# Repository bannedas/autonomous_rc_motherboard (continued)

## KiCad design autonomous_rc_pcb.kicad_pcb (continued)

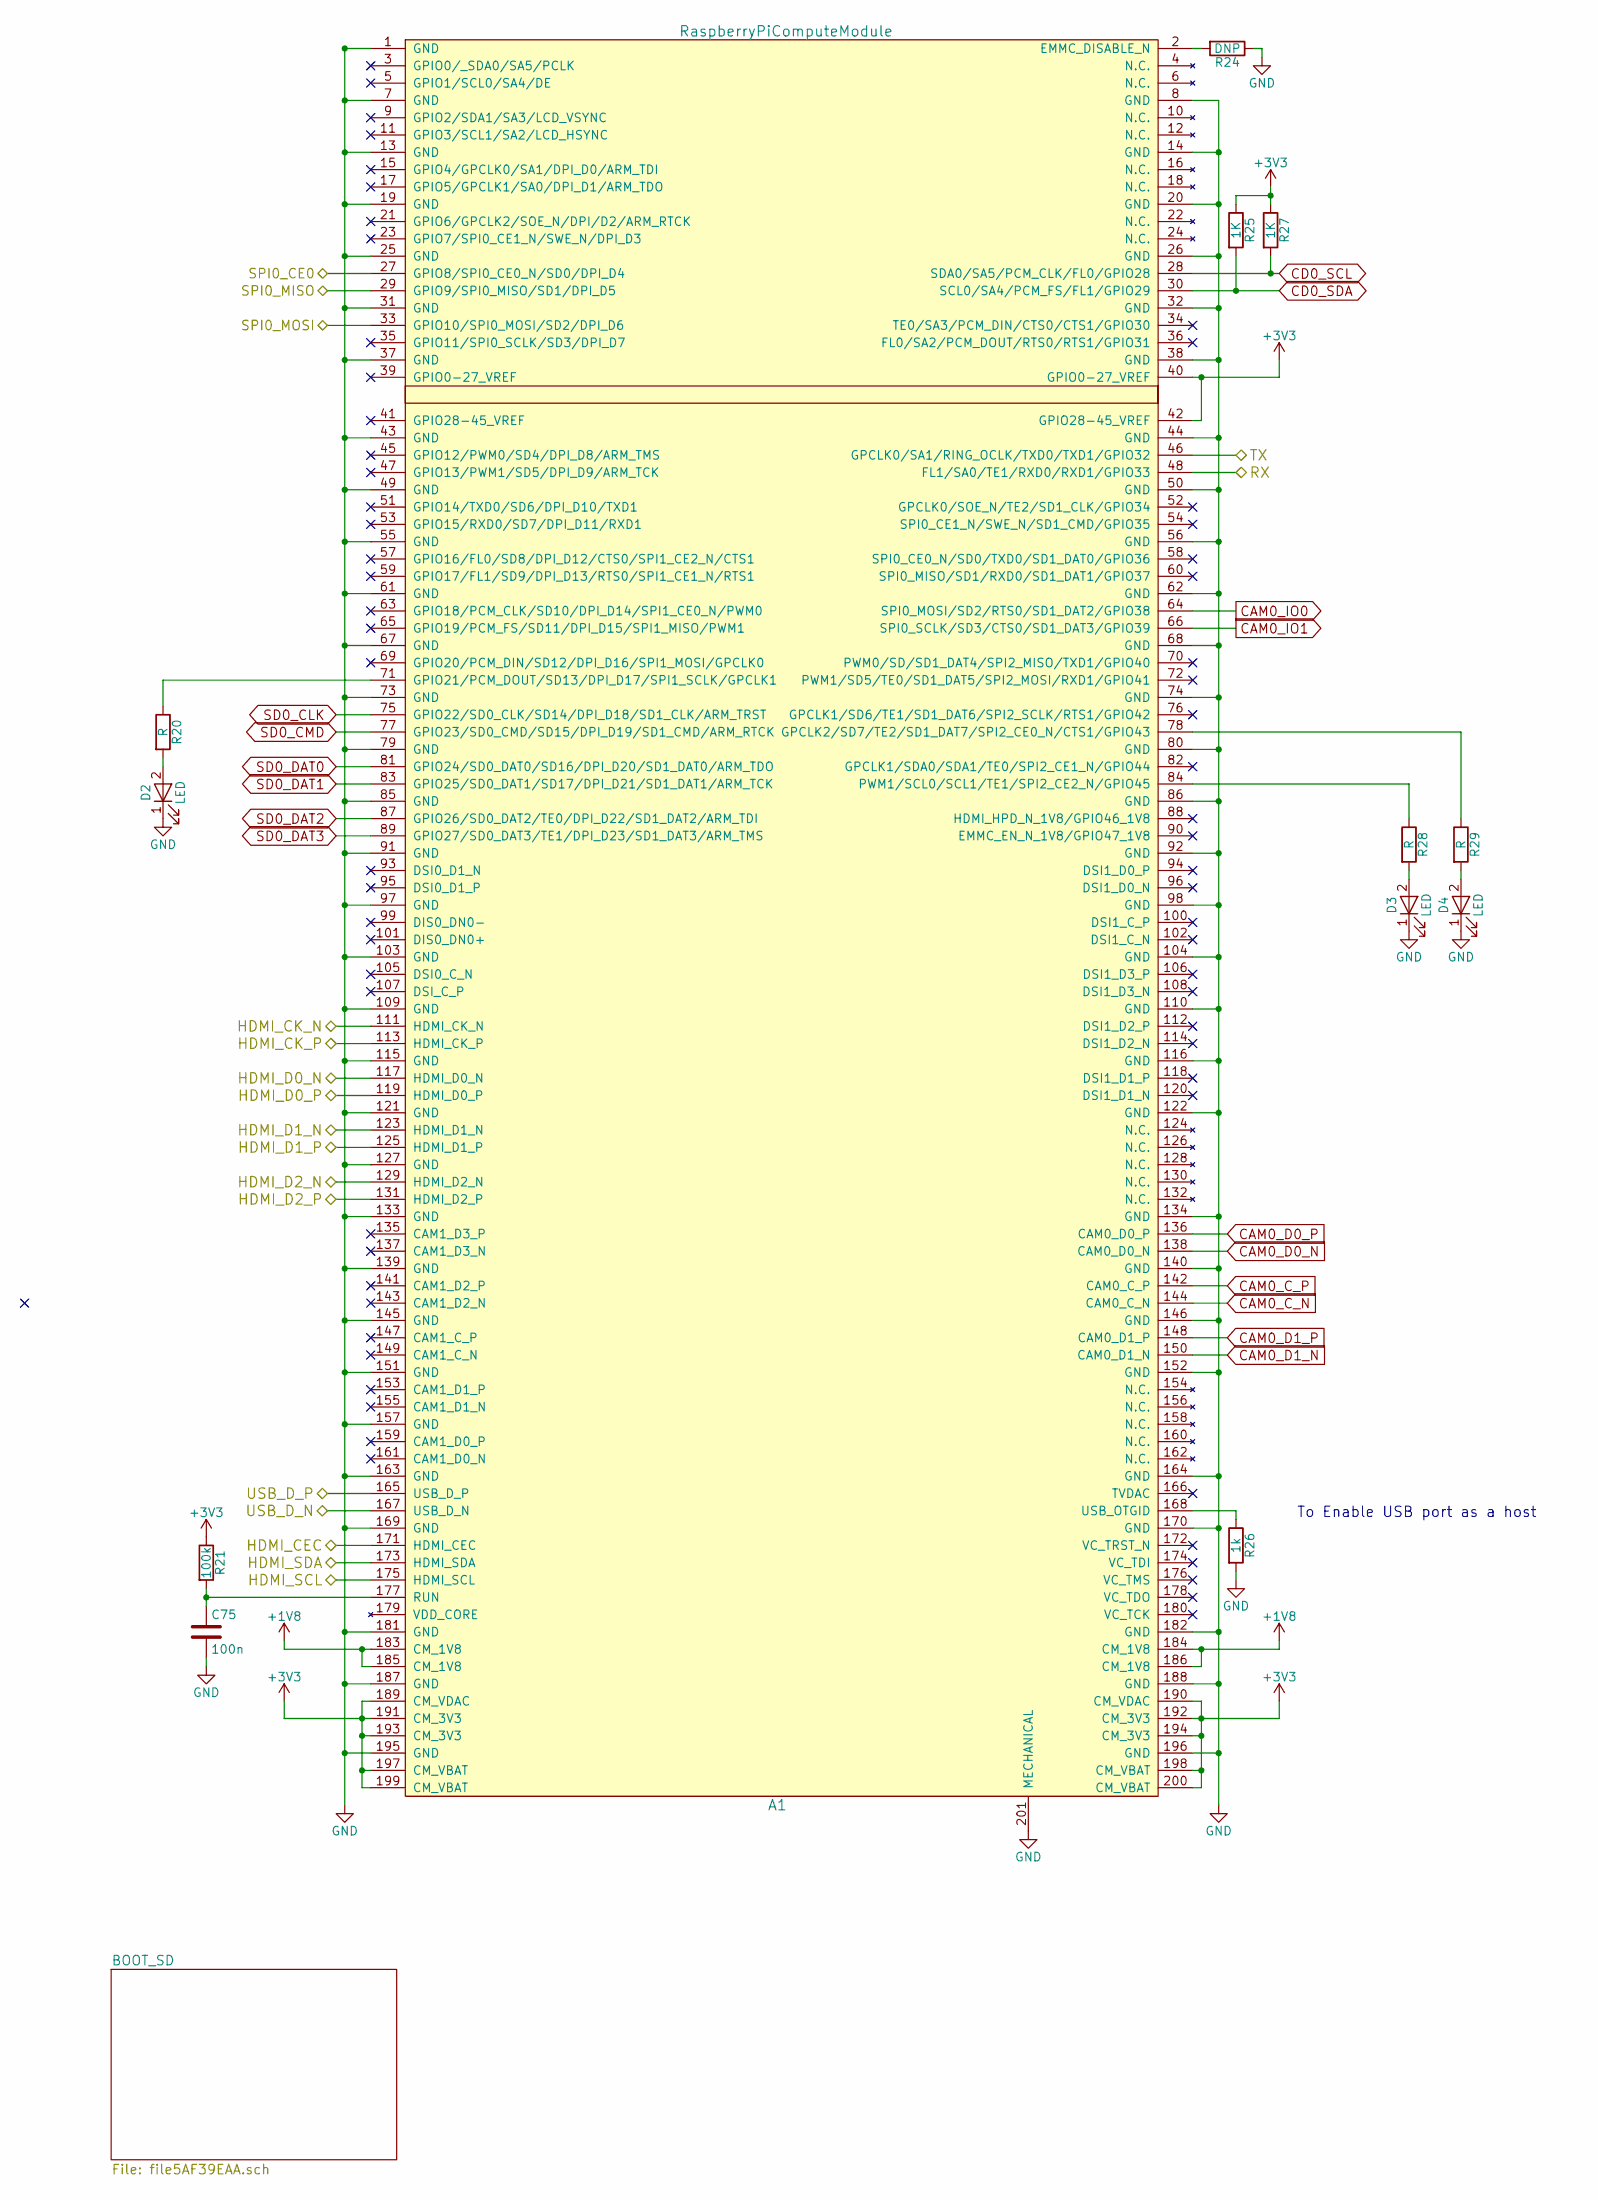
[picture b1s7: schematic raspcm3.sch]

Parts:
A1: RaspberryPiComputeModule; DDR2_TE_1473149-4
C75: 100n; C_0402
D2, D3, D4: LED; LED_0603
R20, R28, R29: R; R_0402
R21: 100k; R_0402
R24: DNP; R_0402
R25, R27: 1K; R_0402
R26: 1k; R_0402

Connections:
+1V8: A1.183 (CM_1V8), A1.184 (CM_1V8), A1.185 (CM_1V8), A1.186 (CM_1V8); also elsewhere on the board
/STM_RESET: A1.33 (GPIO10/SPI0_MOSI/SD2/DPI_D6); also elsewhere on the board
/STM_SWCLK: A1.27 (GPIO8/SPI0_CE0_N/SD0/DPI_D4); also elsewhere on the board
/STM_SWDIO: A1.29 (GPIO9/SPI0_MISO/SD1/DPI_D5); also elsewhere on the board
/UART_RX_GPS_RASP: A1.48 (FL1/SA0/TE1/RXD0/RXD1/GPIO33); also elsewhere on the board
/UART_TX_GPS_RASP: A1.46 (GPCLK0/SA1/RING_OCLK/TXD0/TXD1/GPIO32); also elsewhere on the board
/USB_HUB+: A1.165 (USB_D_P); also elsewhere on the board
/USB_HUB-: A1.167 (USB_D_N); also elsewhere on the board
/raspcm3/HDMI_CEC: A1.171 (HDMI_CEC); also elsewhere on the board
/raspcm3/HDMI_CK_N: A1.111 (HDMI_CK_N); also elsewhere on the board
/raspcm3/HDMI_CK_P: A1.113 (HDMI_CK_P); also elsewhere on the board
/raspcm3/HDMI_D0_N: A1.117 (HDMI_D0_N); also elsewhere on the board
/raspcm3/HDMI_D0_P: A1.119 (HDMI_D0_P); also elsewhere on the board
/raspcm3/HDMI_D1_N: A1.123 (HDMI_D1_N); also elsewhere on the board
/raspcm3/HDMI_D1_P: A1.125 (HDMI_D1_P); also elsewhere on the board
/raspcm3/HDMI_D2_N: A1.129 (HDMI_D2_N); also elsewhere on the board
/raspcm3/HDMI_D2_P: A1.131 (HDMI_D2_P); also elsewhere on the board
/raspcm3/HDMI_SCL: A1.175 (HDMI_SCL); also elsewhere on the board
/raspcm3/HDMI_SDA: A1.173 (HDMI_SDA); also elsewhere on the board
CAM0_C_N: A1.144 (CAM0_C_N); also elsewhere on the board
CAM0_C_P: A1.142 (CAM0_C_P); also elsewhere on the board
CAM0_D0_N: A1.138 (CAM0_D0_N); also elsewhere on the board
CAM0_D0_P: A1.136 (CAM0_D0_P); also elsewhere on the board
CAM0_D1_N: A1.150 (CAM0_D1_N); also elsewhere on the board
CAM0_D1_P: A1.148 (CAM0_D1_P); also elsewhere on the board
CAM0_IO0: A1.64 (SPI0_MOSI/SD2/RTS0/SD1_DAT2/GPIO38); also elsewhere on the board
CAM0_IO1: A1.66 (SPI0_SCLK/SD3/CTS0/SD1_DAT3/GPIO39); also elsewhere on the board
CD0_SCL: A1.28 (SDA0/SA5/PCM_CLK/FL0/GPIO28), R27.2; also elsewhere on the board
CD0_SDA: A1.30 (SCL0/SA4/PCM_FS/FL1/GPIO29), R25.2; also elsewhere on the board
GND: A1.1 (GND), A1.7 (GND), A1.8 (GND), A1.13 (GND), A1.14 (GND), A1.19 (GND), A1.20 (GND), A1.25 (GND), A1.26 (GND), A1.31 (GND), A1.32 (GND), A1.37 (GND), A1.38 (GND), A1.43 (GND), A1.44 (GND), A1.49 (GND), A1.50 (GND), A1.55 (GND), A1.56 (GND), A1.61 (GND), A1.62 (GND), A1.67 (GND), A1.68 (GND), A1.73 (GND), A1.74 (GND), A1.79 (GND), A1.80 (GND), A1.85 (GND), A1.86 (GND), A1.91 (GND), A1.92 (GND), A1.97 (GND), A1.98 (GND), A1.103 (GND), A1.104 (GND), A1.109 (GND), A1.110 (GND), A1.115 (GND), A1.116 (GND), A1.121 (GND), A1.122 (GND), A1.127 (GND), A1.133 (GND), A1.134 (GND), A1.139 (GND), A1.140 (GND), A1.145 (GND), A1.146 (GND), A1.151 (GND), A1.152 (GND), A1.157 (GND), A1.163 (GND), A1.164 (GND), A1.169 (GND), A1.170 (GND), A1.181 (GND), A1.182 (GND), A1.187 (GND), A1.188 (GND), A1.195 (GND), A1.196 (GND), A1.201 (MECHANICAL), C75.2, D2.1 (K), D3.1 (K), D4.1 (K), R24.1, R26.2; also elsewhere on the board
unnamed: A1.2 (EMMC_DISABLE_N), R24.2
unnamed: A1.71 (GPIO21/PCM_DOUT/SD13/DPI_D17/SPI1_SCLK/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), R20.1
unnamed: A1.78 (GPCLK2/SD7/TE2/SD1_DAT7/SPI2_CE0_N/CTS1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), R29.1
unnamed: A1.84 (PWM1/SCL0/SCL1/TE1/SPI2_CE2_N/GPIO45), R28.1
unnamed: A1.168 (USB_OTGID), R26.1
unnamed: A1.177 (RUN), C75.1, R21.2
unnamed: D2.2 (A), R20.2
unnamed: D3.2 (A), R28.2
unnamed: D4.2 (A), R29.2
SD0_CLK: A1.75 (GPIO22/SD0_CLK/SD14/DPI_D18/SD1_CLK/ARM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); also elsewhere on the board
SD0_CMD: A1.77 (GPIO23/SD0_CMD/SD15/DPI_D19/SD1_CMD/ARM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); also elsewhere on the board
SD0_DAT0: A1.81 (GPIO24/SD0_DAT0/SD16/DPI_D20/SD1_DAT0/A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); also elsewhere on the board
SD0_DAT1: A1.83 (GPIO25/SD0_DAT1/SD17/DPI_D21/SD1_DAT1/A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); also elsewhere on the board
SD0_DAT2: A1.87 (GPIO26/SD0_DAT2/TE0/DPI_D22/SD1_DAT2/AR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); also elsewhere on the board
SD0_DAT3: A1.89 (GPIO27/SD0_DAT3/TE1/DPI_D23/SD1_DAT3/AR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); also elsewhere on the board

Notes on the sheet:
To Enable USB port as a host

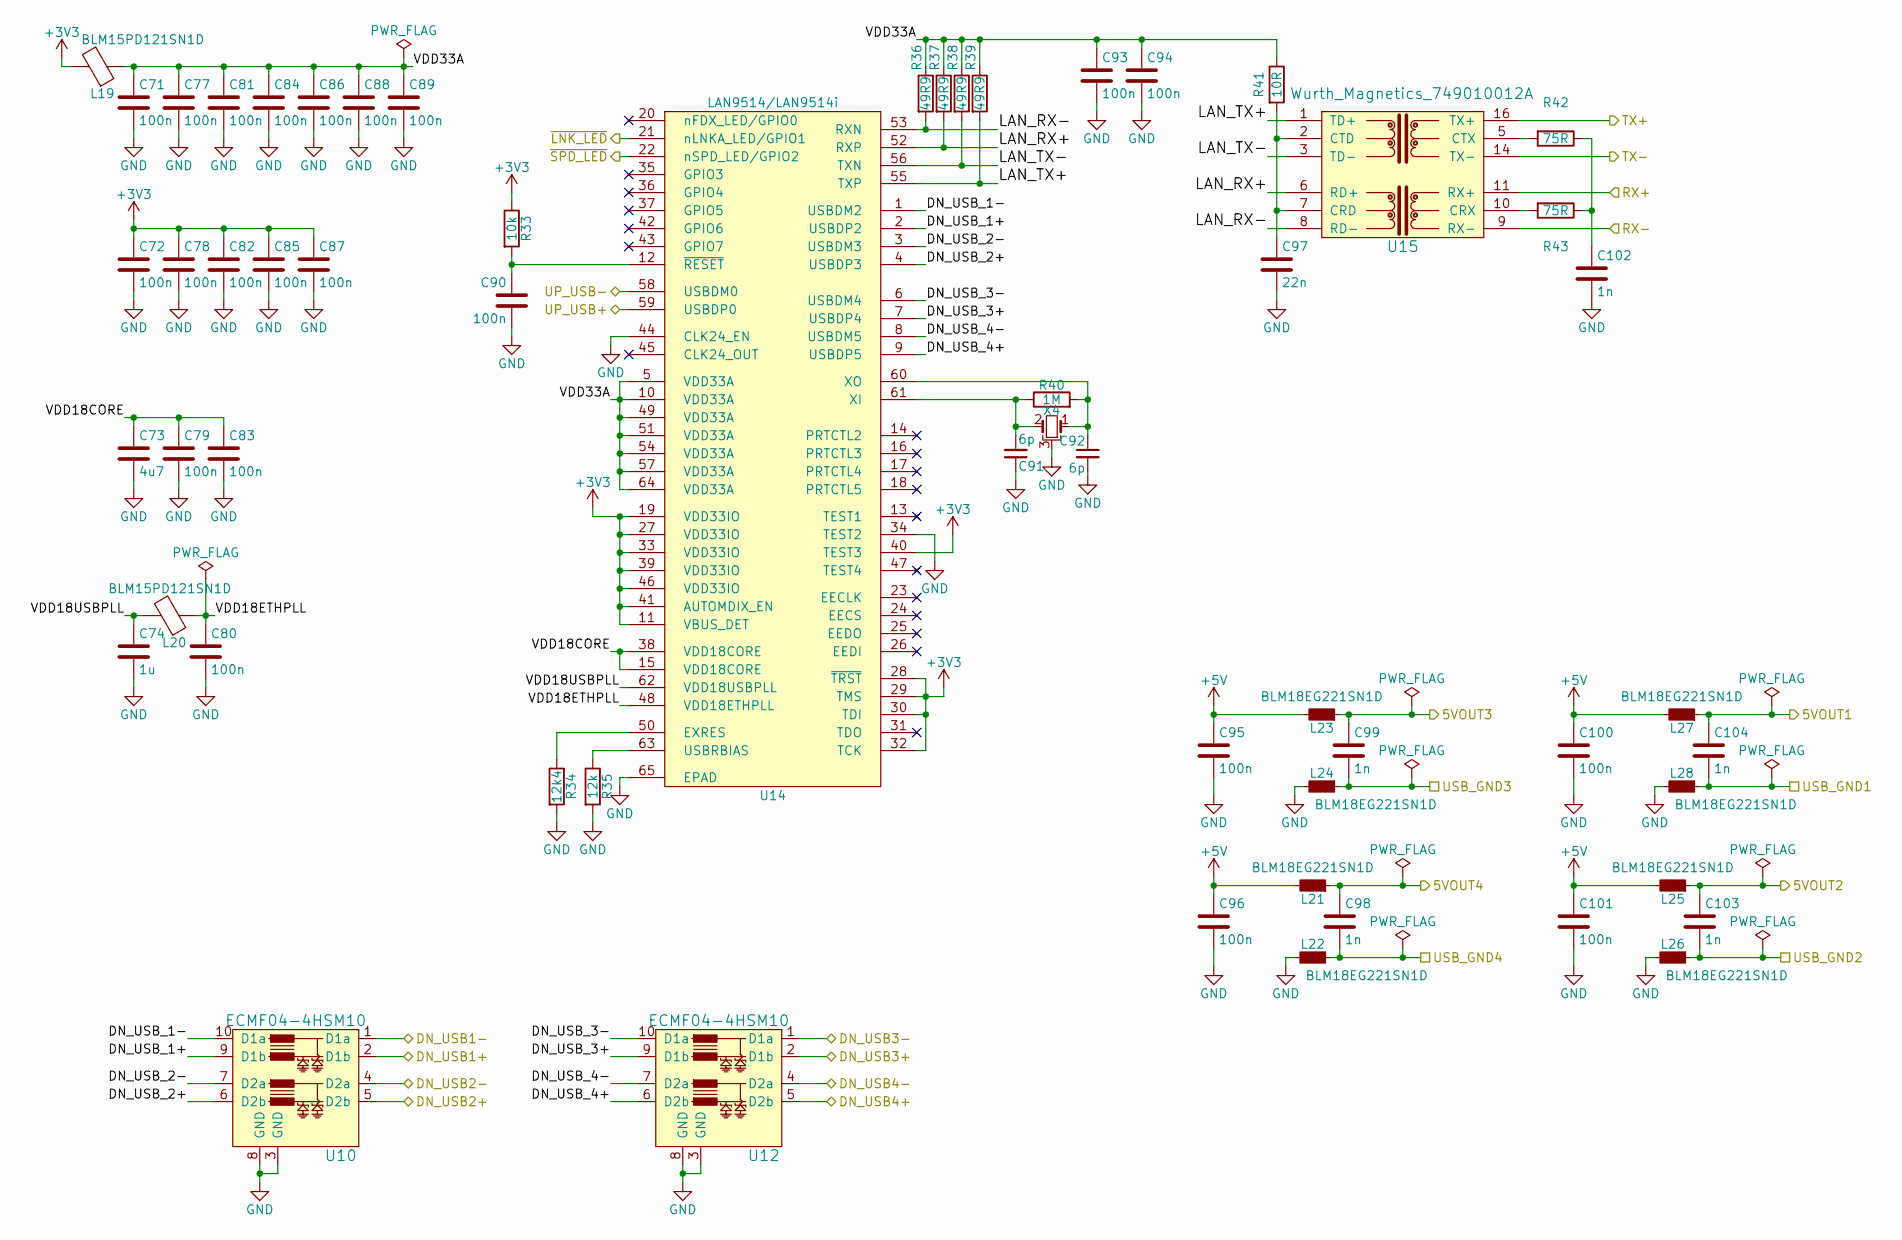
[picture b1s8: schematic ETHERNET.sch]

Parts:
C71, C72, C77, C78, C79, C80, C81, C82, C83, C84, C85, C86, C87, C88, C89, C90, C93, C94, C95, C96, C100, C101: 100n; C_0402
C73: 4u7; C_0603
C74: 1u; C_0402
C91, C92: 6p; C_0402
C97: 22n; C_0805
C98, C99, C103, C104: 1n; C_0402
C102: 1n; C_0805
L19, L20: BLM15PD121SN1D; R_0402
L21, L22, L23, L24, L25, L26, L27, L28: BLM18EG221SN1D; R_0603; MPN BLM18EG221SN1D
R33: 10k; R_0402
R34: 12k4; R_0402
R35: 12k; R_0402
R36, R37, R38, R39: 49R9; R_0402
R40: 1M; R_0402
R41: 10R; R_0402
R42, R43: 75R; R_0402
U10, U12: ECMF04-4HSM10; UDFN-10_1.35x2.6mm_Pitch0.5mm; MPN ECMF04-4HSM10
U14: LAN9514/LAN9514i; QFN-64-1EP_9x9mm_Pitch0.5mm; MPN LAN9514-JZX
U15: Wurth_Magnetics_749010012A; Wurth_749010012A; MPN 749010012A
X4: XRCGB25M000F2P00R0; XRCGB

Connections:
+5V: C95.1, C96.1, C100.1, C101.1, L21.2, L23.2, L25.2, L27.2; also elsewhere on the board
/ETHERNET/5VOUT1: C104.1, L27.1; also elsewhere on the board
/ETHERNET/5VOUT2: C103.1, L25.1; also elsewhere on the board
/ETHERNET/5VOUT3: C99.1, L23.1; also elsewhere on the board
/ETHERNET/5VOUT4: C98.1, L21.1; also elsewhere on the board
/ETHERNET/DN_USB1+: U10.2 (D1b); also elsewhere on the board
/ETHERNET/DN_USB1-: U10.1 (D1a); also elsewhere on the board
/ETHERNET/DN_USB2+: U10.5 (D2b); also elsewhere on the board
/ETHERNET/DN_USB2-: U10.4 (D2a); also elsewhere on the board
/ETHERNET/DN_USB3+: U12.2 (D1b); also elsewhere on the board
/ETHERNET/DN_USB3-: U12.1 (D1a); also elsewhere on the board
/ETHERNET/DN_USB4+: U12.5 (D2b); also elsewhere on the board
/ETHERNET/DN_USB4-: U12.4 (D2a); also elsewhere on the board
/ETHERNET/DN_USB_1+: U10.9 (D1b), U14.2 (USBDP2)
/ETHERNET/DN_USB_1-: U10.10 (D1a), U14.1 (USBDM2)
/ETHERNET/DN_USB_2+: U10.6 (D2b), U14.4 (USBDP3)
/ETHERNET/DN_USB_2-: U10.7 (D2a), U14.3 (USBDM3)
/ETHERNET/DN_USB_3+: U12.9 (D1b), U14.7 (USBDP4)
/ETHERNET/DN_USB_3-: U12.10 (D1a), U14.6 (USBDM4)
/ETHERNET/DN_USB_4+: U12.6 (D2b), U14.9 (USBDP5)
/ETHERNET/DN_USB_4-: U12.7 (D2a), U14.8 (USBDM5)
/ETHERNET/LAN_RX+: R37.2, U14.52 (RXP), U15.6 (RD+)
/ETHERNET/LAN_RX-: R36.2, U14.53 (RXN), U15.8 (RD-)
/ETHERNET/LAN_TX+: R39.2, U14.55 (TXP), U15.1 (TD+)
/ETHERNET/LAN_TX-: R38.2, U14.56 (TXN), U15.3 (TD-)
/ETHERNET/RX+: U15.11 (RX+); also elsewhere on the board
/ETHERNET/RX-: U15.9 (RX-); also elsewhere on the board
/ETHERNET/TX+: U15.16 (TX+); also elsewhere on the board
/ETHERNET/TX-: U15.14 (TX-); also elsewhere on the board
/ETHERNET/USB_GND1: C104.2, L28.1; also elsewhere on the board
/ETHERNET/USB_GND2: C103.2, L26.1; also elsewhere on the board
/ETHERNET/USB_GND3: C99.2, L24.1; also elsewhere on the board
/ETHERNET/USB_GND4: C98.2, L22.1; also elsewhere on the board
/ETHERNET/VDD18CORE: C73.1, C79.1, C83.1, U14.15 (VDD18CORE), U14.38 (VDD18CORE)
/ETHERNET/VDD18ETHPLL: C80.1, L20.1, U14.48 (VDD18ETHPLL)
/ETHERNET/VDD18USBPLL: C74.1, L20.2, U14.62 (VDD18USBPLL)
/ETHERNET/VDD33A: C71.1, C77.1, C81.1, C84.1, C86.1, C88.1, C89.1, C93.1, C94.1, L19.1, R36.1, R37.1, R38.1, R39.1, R41.1, U14.5 (VDD33A), U14.10 (VDD33A), U14.49 (VDD33A), U14.51 (VDD33A), U14.54 (VDD33A), U14.57 (VDD33A), U14.64 (VDD33A)
/ETHERNET/~LNK_LED: U14.21 (nLNKA_LED/GPIO1); also elsewhere on the board
/ETHERNET/~SPD_LED: U14.22 (nSPD_LED/GPIO2); also elsewhere on the board
/USB_ETHER+: U14.59 (USBDP0); also elsewhere on the board
/USB_ETHER-: U14.58 (USBDM0); also elsewhere on the board
GND: C71.2, C72.2, C73.2, C74.2, C77.2, C78.2, C79.2, C80.2, C81.2, C82.2, C83.2, C84.2, C85.2, C86.2, C87.2, C88.2, C89.2, C90.2, C91.1, C92.2, C93.2, C94.2, C95.2, C96.2, C97.2, C100.2, C101.2, C102.2, L22.2, L24.2, L26.2, L28.2, R34.2, R35.2, U10.3 (GND), U10.8 (GND), U12.3 (GND), U12.8 (GND), U14.34 (TEST2), U14.44 (CLK24_EN), U14.65 (EPAD), X4.3; also elsewhere on the board
unnamed: C90.1, R33.2, U14.12 (~RESET)
unnamed: C91.2, R40.1, U14.61 (XI), X4.2
unnamed: C92.1, R40.2, U14.60 (XO), X4.1
unnamed: C97.1, R41.2, U15.2 (CTD), U15.7 (CRD)
unnamed: C102.1, R42.1, R43.1
unnamed: R34.1, U14.50 (EXRES)
unnamed: R35.1, U14.63 (USBRBIAS)
unnamed: R42.2, U15.5 (CTX)
unnamed: R43.2, U15.10 (CRX)

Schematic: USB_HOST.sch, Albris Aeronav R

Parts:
C59, C60, C61, C62, C63, C65, C66, C69, C70: 100n; C_0402
C64: 9p; C_0603_1608Metric; MPN GRM1555C1H9R0CA01D
C67: 9p; C_0603_1608Metric
C68: 4u7 10V; C_0603
R14, R16, R17, R18, R19: 100k; R_0402
R15: 12k0; R_0402
U13: USB2514Bi; QFN36_5m5X5m5; MPN USB2514B/M2
X3: XRCGB24M000F2P00R0; XRCGB

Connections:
/STM_USB_N: U13.1 (USBDM_DN1/PRT_DIS_M1); also elsewhere on the board
/STM_USB_P: U13.2 (USBDP_DN1/PRT_DIS_P1); also elsewhere on the board
/UBLOX_USB+: U13.4 (USBDP_DN2/PRT_DIS_P2); also elsewhere on the board
/UBLOX_USB-: U13.3 (USBDM_DN2/PRT_DIS_M2); also elsewhere on the board
/USB_ETHER+: U13.7 (USBDP_DN3/PRT_DIS_P3); also elsewhere on the board
/USB_ETHER-: U13.6 (USBDM_DN3/PRT_DIS_M3); also elsewhere on the board
/USB_HUB+: U13.31 (USBUP_DP); also elsewhere on the board
/USB_HUB-: U13.30 (USBUP_DM); also elsewhere on the board
GND: C59.2, C60.2, C61.2, C62.2, C63.2, C64.1, C65.2, C66.2, C67.1, C68.2, C69.2, C70.2, R15.1, R16.2, R17.2, R18.2, R19.2, U13.37 (VSS(PAD)), X3.3; also elsewhere on the board
unnamed: C64.2, U13.33 (XTALIN/CLKIN), X3.1
unnamed: C66.1, R14.1, U13.26 (RESET_N)
unnamed: C67.2, U13.32 (XTALOUT), X3.2
unnamed: C69.1, U13.34 (PLLFILT)
unnamed: C70.1, U13.14 (CRFILT)
unnamed: R15.2, U13.35 (RBIAS)
unnamed: R16.1, U13.22 (SDA/SMBDATA/NON_REM1)
unnamed: R17.1, U13.28 (SUSP_IND/LOCAL_PWR/NON_REM0)
unnamed: R18.1, U13.25 (HS_IND/CFG_SEL1)
unnamed: R19.1, U13.24 (SCL/SMBCLK/CFG_SEL0)

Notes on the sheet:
pin 15

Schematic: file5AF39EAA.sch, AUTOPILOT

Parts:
C76: 100n; C_0402
J9: Micro_SD_Card; microSD_Card_Receptacle_Wurth_693072010801
U11: CM1624; UDFN-16-1EP_3.3x1.35mm_Pitch0.4mm

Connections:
GND: C76.2, J9.6 (VSS), J9.9 (SHIELD), U11.17 (GND); also elsewhere on the board
unnamed: C76.1, J9.4 (VDD), U11.4 (SDESD1)
unnamed: J9.1 (DAT2), U11.8 (SDData2)
unnamed: J9.2 (DAT3/CD), U11.7 (SDData3)
unnamed: J9.3 (CMD), U11.6 (SDCMD)
unnamed: J9.5 (CLK), U11.3 (SDCLK)
unnamed: J9.7 (DAT0), U11.2 (SDData0)
unnamed: J9.8 (DAT1), U11.1 (SDData1)
SD0_CLK: U11.14 (CLK); also elsewhere on the board
SD0_CMD: U11.11 (CMD); also elsewhere on the board
SD0_DAT0: U11.15 (DATA0); also elsewhere on the board
SD0_DAT1: U11.16 (DATA1); also elsewhere on the board
SD0_DAT2: U11.9 (Data2); also elsewhere on the board
SD0_DAT3: U11.10 (Data3); also elsewhere on the board

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
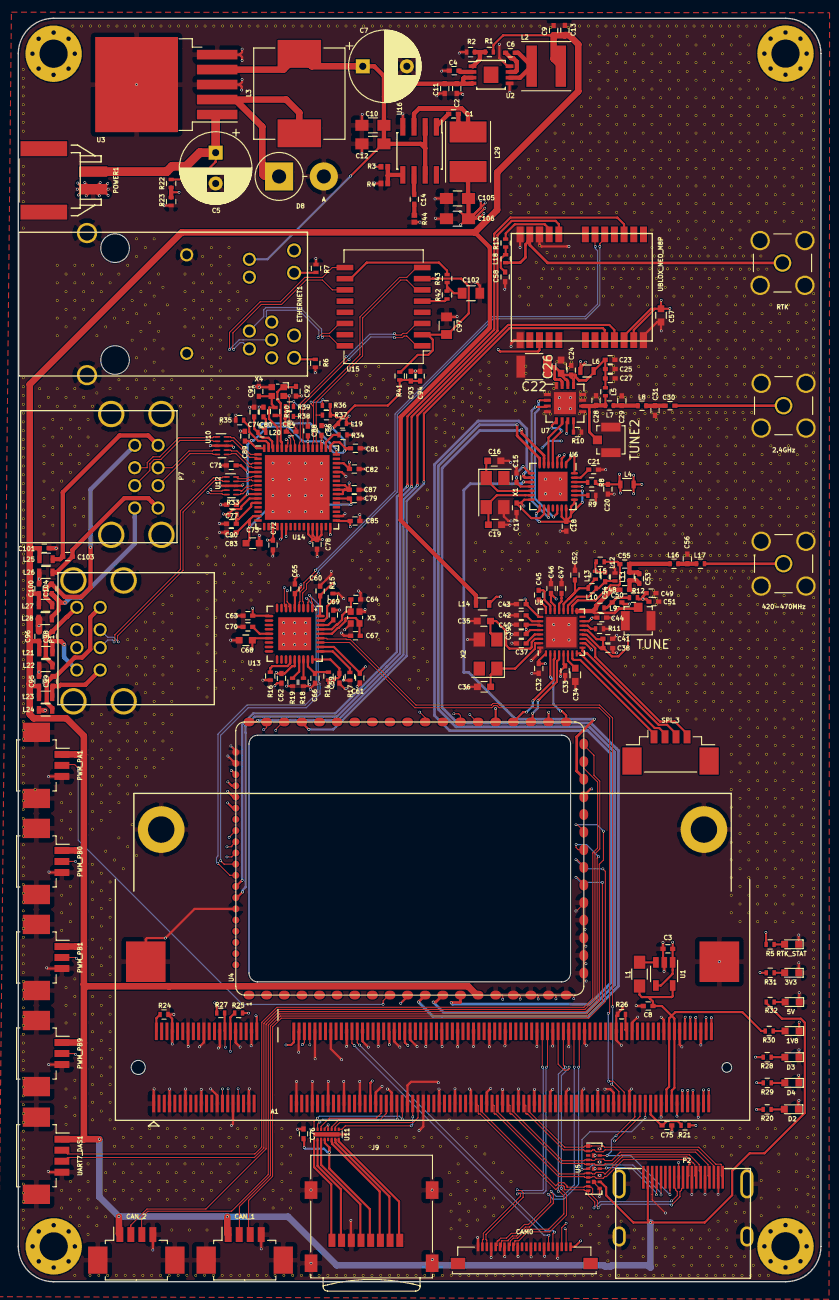
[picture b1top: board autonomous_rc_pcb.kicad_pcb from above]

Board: 6 copper layers, 91.1 x 143.4 mm, 228 parts (0 on the bottom side), 209 nets.

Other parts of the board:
2.4GHz, 420-470MHz: SMA_SMD; SMA_THT_Jack_Straight
5V: 5V; LED_0603
P7: USB_A_Vertical; USB_A_Stacked
RTK: SMA_SMD; SMA_THT_Jack_Straight
RTK_STAT: RTK_STAT; LED_0603
TUNE, TUNE2: U.FL-R-SMT
UBLOX_NEO_M8P: UBLOX_NEO_M8P; U-BLOX-NEO-M8P

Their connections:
/ETHERNET/5VOUT1: P7.1; also elsewhere on the board
/ETHERNET/5VOUT2: P7.6; also elsewhere on the board
/ETHERNET/DN_USB1+: P7.3; also elsewhere on the board
/ETHERNET/DN_USB1-: P7.2; also elsewhere on the board
/ETHERNET/DN_USB2+: P7.8; also elsewhere on the board
/ETHERNET/DN_USB2-: P7.7; also elsewhere on the board
/ETHERNET/USB_GND1: P7.4; also elsewhere on the board
/ETHERNET/USB_GND2: P7.9; also elsewhere on the board
/UBLOX/RTK_STAT: UBLOX_NEO_M8P.15; also elsewhere on the board
/UBLOX/RX: UBLOX_NEO_M8P.21; also elsewhere on the board
/UBLOX/TX: UBLOX_NEO_M8P.20; also elsewhere on the board
/UBLOX_USB+: UBLOX_NEO_M8P.6; also elsewhere on the board
/UBLOX_USB-: UBLOX_NEO_M8P.5; also elsewhere on the board
/das_board/PC8: UBLOX_NEO_M8P.8; also elsewhere on the board
/das_board/PC9: UBLOX_NEO_M8P.3; also elsewhere on the board
GND: 2.4GHz.2, 5V.1, 420-470MHz.2, P7.5, RTK.2, RTK_STAT.1, TUNE.2, TUNE2.2, UBLOX_NEO_M8P.10, UBLOX_NEO_M8P.12, UBLOX_NEO_M8P.13, UBLOX_NEO_M8P.24; also elsewhere on the board
unnamed 216: TUNE2.1; also elsewhere on the board
unnamed 218: 2.4GHz.1; also elsewhere on the board
unnamed 229: TUNE.1; also elsewhere on the board
unnamed 253: RTK_STAT.2; also elsewhere on the board
unnamed 259: 5V.2; also elsewhere on the board
unnamed 273: 420-470MHz.1; also elsewhere on the board
unnamed 274: RTK.1, UBLOX_NEO_M8P.11; also elsewhere on the board
unnamed 283: UBLOX_NEO_M8P.9; also elsewhere on the board

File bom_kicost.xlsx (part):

Prj: | bom_kicost.xml |  |  |  | Board Qty: | 100
Co.: |  |  |  |  | Unit Cost: | 0
Prj date: | Thu 24 May 2018 02:57:31 PM CEST |  |  |  | Total Cost: | 0 |  |  |  | 0 | 0 |  |  |  | 0 | 0 |  |  |  | 0 | 0 |  |  |  | 0 | 0 |  |  |  | 0 | 0 |  |  |  | 0 | 0
$ date: | 2018-05-24 14:59:21
Global Part Info |  |  |  |  |  |  | Digi-Key |  |  |  |  | Farnell |  |  |  |  | Mouser |  |  |  |  | Newark |  |  |  |  | Rs Components |  |  |  |  | Tme
Refs | Value | Footprint | Manf# | Qty | Unit$ | Ext$ | Avail | Purch | Unit$ | Ext$ | Cat# | Avail | Purch | Unit$ | Ext$ | Cat# | Avail | Purch | Unit$ | Ext$ | Cat# | Avail | Purch | Unit$ | Ext$ | Cat# | Avail | Purch | Unit$ | Ext$ | Cat# | Avail | Purch | Unit$ | Ext$ | Cat#
A1 | RaspberryPiComputeModule | Don-Con:DDR2_TE_1473149-4 |  | 0 | 0 | 0
C1 | 10nF | Capacitors_SMD:C_0402 |  | 0 | 0 | 0
C10,C12 | 10uF | Capacitors_SMD:C_0805_HandSoldering |  | 0 | 0 | 0
C102 | 1n | Capacitors_SMD:C_0805 |  | 0 | 0 | 0
C105,C106 | 22uF | Capacitors_SMD:C_0805_HandSoldering |  | 0 | 0 | 0
C14 | 3.3nF | Capacitors_SMD:C_0402 |  | 0 | 0 | 0
C16,C19 | 15pF | Capacitors_SMD:C_0603 |  | 0 | 0 | 0
C2,C9,C11,C13 | 10uF | Capacitors_SMD:C_0402 |  | 0 | 0 | 0
C20,C23,C26 | 2.2uF | Capacitors_SMD:C_0402 |  | 0 | 0 | 0
C22 | 12uF | Capacitors_SMD:C_0402 |  | 0 | 0 | 0
C24,C25 | 1nF | Capacitors_SMD:C_0402 |  | 0 | 0 | 0
C27 | 12pF | Capacitors_SMD:C_0402 |  | 0 | 0 | 0
C28,C29,C53 | 2.2pF | Capacitors_SMD:C_0402 |  | 0 | 0 | 0
C3,C8 | 4.7uF | Capacitors_SMD:C_0402 |  | 0 | 0 | 0
C30 | 18pF | Capacitors_SMD:C_0402 |  | 0 | 0 | 0
C31 | 0.2pF | Capacitors_SMD:C_0402 |  | 0 | 0 | 0
C34,C57 | 2.2uF | Capacitors_SMD:C_0603 |  | 0 | 0 | 0
C35,C36 | 15p | Capacitors_SMD:C_0603 |  | 0 | 0 | 0
C4 | 1uF | Capacitors_SMD:C_0402 |  | 0 | 0 | 0
C45 | 1.8nF | Capacitors_SMD:C_0402 |  | 0 | 0 | 0
C48 | 39pF | Capacitors_SMD:C_0402 |  | 0 | 0 | 0
C5 | 100uF | Capacitor_THT:CP_Radial_D8.0mm_P3.50mm |  | 0 | 0 | 0
C50 | 56pF | Capacitors_SMD:C_0402 |  | 0 | 0 | 0
C52,C54,C55 | 5.1pF | Capacitors_SMD:C_0402 |  | 0 | 0 | 0
C56 | 6.2pF | Capacitors_SMD:C_0402 |  | 0 | 0 | 0
C6,C15,C17,C18,C21,C32,C33,C37-C44,C46,C47,C49,C51,C58 | 100nF | Capacitors_SMD:C_0402 |  | 0 | 0 | 0
C64,C67 | 9p | Capacitors_SMD:C_0402 | GRM1555C1H9R0CA01D | 0 | 0 | 0 | NonStk |  | 0 | 0 | 490-8232-1-ND |  |  |  |  |  | NonStk |  | 0 | 0 | 81-GRM1555C1H9R0CA1D
C68 | 4u7 10V | Capacitors_SMD:C_0603 |  | 0 | 0 | 0
C7 | 1000uF | Capacitor_THT:CP_Radial_D8.0mm_P5.00mm | EEUFR1C102LB | 0 | 0 | 0 | 860 |  | 0 | 0 | P15332CT-ND |  |  |  |  |  | NonStk |  | 0 | 0 | 667-EEU-FR1C102LB | 263 |  | 0 | 0 | 49W7393 | 3800 |  |  |  | 708-3642
C73 | 4u7 | Capacitors_SMD:C_0603 |  | 0 | 0 | 0
C74 | 1u | Capacitors_SMD:C_0402 |  | 0 | 0 | 0
C91,C92 | 6p | Capacitors_SMD:C_0402 |  | 0 | 0 | 0
C97 | 22n | Capacitors_SMD:C_0805 |  | 0 | 0 | 0
C98,C99,C103,C104 | 1n | Capacitors_SMD:C_0402 |  | 0 | 0 | 0
C59-C63,C65,C66,C69-C72,C76-C90,C93-C96,C100,C101 | 100n | Capacitors_SMD:C_0402 |  | 0 | 0 | 0
CAM0 | Conn_01x22 | MM-CONN:54548-2271 | 54548-2271 | 0 | 0 | 0 | 5312 |  | 0 | 0 | WM8828CT-ND |  |  |  |  |  | 2773 |  | 0 | 0 | 538-54548-2271 | 24750 |  | 0 | 0 | 28W0905
CAN_1,CAN_2,UART7_DAS1 | CONN_01X04 | Connectors_Molex:Molex_PicoBlade_53261-0471_04x1.25mm_Angled |  | 0 | 0 | 0
D1 | RTK_STAT | LEDs:LED_0603 |  | 0 | 0 | 0
D5,D6 | 3V3 | LEDs:LED_0603 |  | 0 | 0 | 0
D7 | 5V | LEDs:LED_0603 |  | 0 | 0 | 0
D8 | 1N5822 | PAUL-DIODE-SMD:D_DO-201AD_P5.08mm_Vertical_AnodeUp |  | 0 | 0 | 0
D2-D4 | LED | LEDs:LED_0603 |  | 0 | 0 | 0
ETHERNET1 | 08261L1T57-F | FS-Conn:0826-1L1T-57-F | 08261L1T57-F | 0 | 0 | 0 | 1929 |  | 0 | 0 | 507-1431-ND |  |  |  |  |  | 757 |  | 0 | 0 | 530-0826-1L1T-57-F
J9 | Micro_SD_Card | Don-Con:microSD_Card_Receptacle_Wurth_693072010801 |  | 0 | 0 | 0
L1 | 4.7uH | Resistors_SMD:R_0805_HandSoldering | CPI0805E4R7R-10 | 0 | 0 | 0 | NonStk |  | 0 | 0 | CPI0805E4R7R-10-ND |  |  |  |  |  | 11435 |  | 0 | 0 | 875-CPI0805E4R7R-10 | 1114 |  | 0 | 0 | 39Y3900
L11,L15 | 15n | Resistors_SMD:R_0402 |  | 0 | 0 | 0
L12,L13 | 27n | Resistors_SMD:R_0402 |  | 0 | 0 | 0
L16 | 43n | Resistors_SMD:R_0402 |  | 0 | 0 | 0
L17 | 22n | Resistors_SMD:R_0402 |  | 0 | 0 | 0
L18 | 56N | Resistors_SMD:R_0402 |  | 0 | 0 | 0
L19,L20 | BLM15PD121SN1D | Resistors_SMD:R_0402 |  | 0 | 0 | 0
L2 | 22uH | Inductors_SMD:L_Coilcraft_XAL5030 | VLCF5020T-220MR75-1 | 0 | 0 | 0 | 21355 |  | 0 | 0 | 445-3211-1-ND |  |  |  |  |  | 6990 |  | 0 | 0 | 810-VLCF52T220MR751 | NonStk |  | 0 | 0 | 91Y7126 | 280 |  | 0 | 0 | 614-2863
L29 | 4.7uH | Inductors_SMD:L_Taiyo-Yuden_NR-50xx_HandSoldering | SRN4018-4R7M | 0 | 0 | 0 | 38373 |  | 0 | 0 | SRN4018-4R7MCT-ND |  |  |  |  |  | 14094 |  | 0 | 0 | 652-SRN4018-4R7M | 4833 |  | 0 | 0 | 54W0064 | NonStk |  | 0 | 0 | 172-8355
L3 | 100uH | Inductors_SMD:L_Vishay_IHLP-4040 | MSS1210-104KED | 0 | 0 | 0 |  |  |  |  |  |  |  |  |  |  | 1939 |  | 0 | 0 | 994-MSS1210-104KED
L4,L6,L14 | BEAD | Resistors_SMD:R_0603 | BLM18HE152SN1 | 0 | 0 | 0 | 94313 |  | 0 | 0 | 490-5216-1-ND |  |  |  |  |  | NonStk |  |  |  | Not Assigned | 23044 |  | 0 | 0 | 87X8574 | NonStk |  | 0 | 0 | 167-4980 | 22000 |  | 0 | 0 | BLM18HE152SN1D
L5 | 4.7n | Resistors_SMD:R_0402 |  | 0 | 0 | 0
L7 | 1n | Resistors_SMD:R_0402 |  | 0 | 0 | 0
L8 | 2n | Resistors_SMD:R_0402 |  | 0 | 0 | 0
L9,L10 | 56n | Resistors_SMD:R_0402 |  | 0 | 0 | 0
L21-L28 | BLM18EG221SN1D | Resistors_SMD:R_0603 | BLM18EG221SN1D | 0 | 0 | 0 | 126995 |  | 0 | 0 | 490-3992-1-ND |  |  |  |  |  |  |  |  |  |  | 6911 |  | 0 | 0 | 73M9090 | 1375 |  | 0 | 0 | 724-1328 | NonStk |  | 0 | 0 | BLM18EG221SN1D
P1,P7 | USB_A_Vertical | Don-Con:USB_A_Stacked |  | 0 | 0 | 0
P2 | HDMI_PAUL | FS-Conn:HDMI_A_47151-1051 |  | 0 | 0 | 0
P3-P5 | SMA_SMD | Connectors:SMA_THT_Jack_Straight |  | 0 | 0 | 0
POWER1 | CONN_01X02 | Don-Con:DuraClik2 |  | 0 | 0 | 0
PWM_PA1,PWM_PB0,PWM_PB1,PWM_PB9 | CONN_01X03 | Connectors_Molex:Molex_PicoBlade_53261-0371_03x1.25mm_Angled |  | 0 | 0 | 0
R1 | 52.3k | Resistors_SMD:R_0402 |  | 0 | 0 | 0
R10 | 3.9K | Resistors_SMD:R_0402 |  | 0 | 0 | 0
R12 | 18R | Resistors_SMD:R_0402 |  | 0 | 0 | 0
R13 | 4.7R | Resistors_SMD:R_0402 |  | 0 | 0 | 0
R14,R16-R19 | 100k | Resistors_SMD:R_0402 |  | 0 | 0 | 0
R15 | 12k0 | Resistors_SMD:R_0402 |  | 0 | 0 | 0
R2,R33 | 10k | Resistors_SMD:R_0402 |  | 0 | 0 | 0
R20,R28,R29 | R | Resistors_SMD:R_0402 |  | 0 | 0 | 0
R22,R40 | 1M | Resistors_SMD:R_0402 |  | 0 | 0 | 0
R23 | 100K | Resistors_SMD:R_0402 |  | 0 | 0 | 0
R24 | DNP | Resistors_SMD:R_0402 |  | 0 | 0 | 0
R26 | 1k | Resistors_SMD:R_0402 |  | 0 | 0 | 0
R3 | 26.1k | Resistor_SMD:R_0402_1005Metric |  | 0 | 0 | 0
R34 | 12k4 | Resistors_SMD:R_0402 |  | 0 | 0 | 0
R35 | 12k | Resistors_SMD:R_0402 |  | 0 | 0 | 0
R4,R44 | 10k | Resistor_SMD:R_0402_1005Metric |  | 0 | 0 | 0
R41 | 10R | Resistors_SMD:R_0402 |  | 0 | 0 | 0
R42,R43 | 75R | Resistors_SMD:R_0402 |  | 0 | 0 | 0
R5,R25,R27,R30-R32 | 1K | Resistors_SMD:R_0402 |  | 0 | 0 | 0
R6,R7 | 120R | Resistors_SMD:R_0402 |  | 0 | 0 | 0
R8 | 10K | Resistors_SMD:R_0402 |  | 0 | 0 | 0
R9,R11 | 56K | Resistors_SMD:R_0402 |  | 0 | 0 | 0
R36-R39 | 49R9 | Resistors_SMD:R_0402 |  | 0 | 0 | 0
SPI_3 | CONN_01X04 | Connectors_Molex:Molex_PicoBlade_53398-0471_04x1.25mm_Straight |  | 0 | 0 | 0
U1 | MCP1603L | TO_SOT_Packages_SMD:TSOT-23-5 | MCP1603LT-180I/OS | 0 | 0 | 0 | NonStk |  | 0 | 0 | MCP1603LT-180I/OS-ND |  |  |  |  |  | NonStk |  | 0 | 0 | 579-MCP1603LT-180IOS
U10,U12 | ECMF04-4HSM10 | Housings_DFN_QFN:UDFN-10_1.35x2.6mm_Pitch0.5mm | ECMF04-4HSM10 | 0 | 0 | 0 | NonStk |  | 0 | 0 | 497-14242-2-ND |  |  |  |  |  | 2949 |  | 0 | 0 | 511-ECMF04-4HSM10 | 3157 |  | 0 | 0 | 41Y1736
U11 | CM1624 | Don-Housing-DFN:UDFN-16-1EP_3.3x1.35mm_Pitch0.4mm | CM1624-08DE | 0 | 0 | 0 | NonStk |  | 0 | 0 | CM1624-08DEOSCT-ND |  |  |  |  |  | NonStk |  | 0 | 0 | 748-CM1624-08DE | NonStk |  | 0 | 0 | 55T2137 | 50 |  | 0 | 0 | 800-9960
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
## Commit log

2018-05-23 beta
    beta pcb version 0.001V
2018-05-24 added rf stitching, connector names
2018-05-24 less stiching, added 3d models
2018-05-24 readme edit
2018-05-24 added bom
2018-05-25 tuned rf
    added u.fl connectors to tune line
    moved some lines under rf components
2018-05-29 stitched pcb, tuned rf
2018-05-29 updated pic
